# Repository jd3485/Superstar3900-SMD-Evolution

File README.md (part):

> **CONTINUITÀ CHATGPT WORK — CONFIGURAZIONE PERMANENTE (11/11/2026).** Nuove sessioni: leggere anzitutto [AGENTS.md](AGENTS.md) (mandato tecnico permanente e ciclo multi-revisione senza ripetere «continua») e [WORK_STATO_CORRENTE.md](00_Gestione_Progetto/WORK_STATO_CORRENTE.md) (checkpoint aggiornabile). Per configurare un Progetto ChatGPT Work usare [ISTRUZIONI_CHATGPT_PROJECT_WORK.md](00_Gestione_Progetto/ISTRUZIONI_CHATGPT_PROJECT_WORK.md). Nessun lavoro prosegue automaticamente dopo la fine della chat senza nuova sessione/attività, e NO FAB/TX resta attivo.

# SUPERSTAR 3900 SMD EVOLUTION — V7.21 PRE-LAYOUT PCB QUALITY GATES (NO FAB / NO TX)

**11 novembre 2026 · V7.21 integrata su `main` tramite [PR #21](https://github.com/jd3485/Superstar3900-SMD-Evolution/pull/21), squash merge `9805f110d0acf59e69f7f54e87e299248b99d96b`.** Decisione di progetto: prima verificare pacchetti reali, pad, alimentazioni e termica, poi creare un'unica PCB. Non promettere «zero errori» sulla base di un DRC non significativo.

**Audit sulla vera netlist KiCad9 a 7 fogli:** **132 componenti**, **84 footprint assegnati**, **48 mancanti** (46 MCU/CODEC, 2 connettori J100/J101 AUX). Fra gli 84 assegnati **F200** fusibile e **Y1** TCXO hanno nomi espliciti `NON_VALIDATO`/`UNVALIDATED`; tutti gli altri footprint non sono ancora vendor-certified. Il nuovo audit ha verificato **sei candidati primari sulle vere librerie KiCad9**: STM32G474RET6 LQFP64 10×10/64 pad, TLV320AIC3204 VQFN32 RHB 5×5/33 pad incluso **EP33**, quattro LDO TPS7A20 DBV SOT23-5/5 pad. CANDIDATI soltanto: nessuno assegnato agli schemi prima del confronto pin/land pattern.

**Rischio TERMICO:** 6 TPS7A2033PDBVR da 300mA max ciascuno, due nella AUX 5V e quattro nella MCU 5V tuttora separata; 5→3,3V a 300mA =0,51W su un LDO, con `RθJA JEDEC=187,1°C/W` DBV e 40°C ambient =`TJ≈135,4°C` nell'esempio, superiore a 125°C operativo. Non prova il consumo effettivo: impone budget corrente e verifica termica PCB. **Buck** TPS54202 2A, R101=100k/R102=13k3 -> nominale `5,077V`, scenario limiti VREF +R `4,863–5,298V`; eFuse TPS26600 limite configurabile e F200 1,5A candidato. Serve qualificare tutti i rail, fuses, input e RTN.

**CI KiCad9** [run 42986310630](https://github.com/jd3485/Superstar3900-SMD-Evolution/actions/runs/42986310630) **success**: **24 test nuovi +284 regressioni=308 Python PASS, 0 FAIL/0 SKIP**. Nessun modificatore di schema o PCB, root ERC **36 errori/340 warning**, 15 RX/MCU/AUX OPEN/HOLD. Artefatti CSV delle 48 impronte mancanti e 6 package candidati, schematics/netlist e JSON in `03_Verifiche/V7.21/`. Rapporto `03_Verifiche/V7.21/RAPPORTO_TECNICO_CAD_V7.21.md`, gate di rilascio `01_Specifiche/V7.21/PIANO_QUALITA_PCB_UNICA_GATES_V7_21.md`, workflow `.github/workflows/v721_full_board_foundations.yml`.

**PCB completa stimata ~10% invariata**, nessuna tavola/meccanica inventata e nessun sbroglio globale simulato. **Next V7.22:** creare versione CAD per i sei IC con pin-pad/EP33 verificati; sistemare 42 missing remaining, poi budget termico/ritorni; solo dopo real PCB unica. **NO FAB / NO GERBER / NO PCBWAY / NO TX**, SG48 e tutti i 15 contratti HOLD.

---

## STORICO README V7.20 E PRECEDENTI

# SUPERSTAR 3900 SMD EVOLUTION — V7.20 PLL NGSPICE / TI 270 CANALI / POWER ERC LEDGER (NO FAB / NO TX)

**11 novembre 2026 · V7.20 MERGED su `main` tramite [PR #20](https://github.com/jd3485/Superstar3900-SMD-Evolution/pull/20), squash commit `271cf7c84c0ceeb1e490ac44ff065147c76fbb4e`.** Ultimo avanzamento è una **verifica analogica del modello** e un audit sulle sei sorgenti POWER della schematica completa, non una PCB unica. **Gli schemi V7.19 e precedenti e il coupon RX rimangono invariati**.

**Evidenza reale:** [CI 42971210346](https://github.com/jd3485/Superstar3900-SMD-Evolution/actions/runs/42971210346) **success**: `ngspice` originale del filtro PLL, **501 punti AC 10Hz–1MHz**, confronto con modello nodale indipendente, errore relativo massimo **8,31×10⁻⁷**, riproduzione del nominale V0.6 4.015,5Hz/59,76° **solo alle ipotesi del modello**, **non TI PLLatinum Sim**. Analizzati tutti **270** canali Integer-N (N3631..3900, fPFD1,28MHz), **2430** casi Kvco/Icp ipotetici; in più secondo sweep su **KVCO tipico ufficiale TI** (SNAS740B Tab.135 Eq.4): 2 canali VCO3 /268 VCO4, CPG4 o8 => nominali 2,5mA senza readback firmware. Nel modello lineare con KVCO tipico: **3,814–4,678kHz crossover**, margine **58,63°–62,87°**, NON limiti garantiti, phase noise/spurie/lock time non simulati.

**Audit KiCad9 nativo sulle 6 alimentazioni senza power-output:** U200:1 `EFUSE_VIN`, U200:8 `EFUSE_RTN`, U2:1 `5V_RF_PREREGULATED`, U2:2 `GND_MAIN`, U6203:1 `5V_DIGITAL_FILTERED`, U6203:2 `GND`. Tutte **HOLD**, nessun PWR_FLAG o waiver, non cortocircuitare GND_MAIN/EFUSE_RTN. Root ERC invariato **36 errori/340 warning**, 15 interfacce OPEN/HOLD. **18 test V7.20 +266 storici=284 Python PASS**, 0 FAIL/skip.

Rapporto e JSON `03_Verifiche/V7.20/`, protocollo TI `01_Specifiche/V7.20/PROTOCOLLO_PLL_NGSPICE_TI_TYPICAL_POWER_HOLD_V7_20.md`, workflow `.github/workflows/v720_pll_spice_power_native.yml`. La PCB completa resta **~10% stimato**, senza sbroglio/routing globale. **Next V7.21:** qualificare 13,8V→eFuse→buck→LDO, ritorni di massa e impostazioni PLL reali, poi PLLatinum Sim / bench e 15 interfacce. **NO FAB / NO GERBER / NO PCBWAY / NO TX**.

---

## STORICO README V7.19 E PRECEDENTI

# SUPERSTAR 3900 SMD EVOLUTION — V7.19 PLL TI LOOP PIN-NET CORRECTION (NO FAB / NO TX)

**11 novembre 2026 · V7.19 integrata su `main` tramite [PR #19](https://github.com/jd3485/Superstar3900-SMD-Evolution/pull/19), squash merge `6d5ccb179cbe46760605edde6c44c2fc89a9ac5e`.** Avanzamento REALE dello schematico KiCad a 7 fogli: nuova copia versionata `04_KiCad/Assemblaggio_RX_Power_V7.19_PLL_PINNET_NOT_FOR_FAB/` con ramo AUX `04_KiCad/Gerarchico_Alimentazioni_V7.19_PLL_PINNET_NOT_FOR_FAB/`. Le versioni passate restano immutate. Nel SOLO foglio PLL sono aggiunte 6 etichette a pin R2/R3/C2/C3: topologia **TI LMX2572 datasheet Fig.179**: CPOUT=U1:12/R2:1/R3:1/C1:2, R2_C2=R2:2/C2:2, VTUNE=U1:35/R3:2/C3:2. Nessun filo, nuova rete di power, intermodulo, TX o PCB aggiunti.

**Prova native KiCad 9:** [CI 42967147073](https://github.com/jd3485/Superstar3900-SMD-Evolution/actions/runs/42967147073) **PASS**: V7.18 42 errori/340 avvisi → V7.19 **36 errori/340 avvisi**, 99→**100 reti** (sola nuova `PLL_R2_C2`), -2 pin_not_connected, -3 wire_dangling, -1 input_not_driven; **nessun ref/pin cambiato fuori da tre reti del filtro**. **13 test nuovi +253 storici =266 Python PASS**, 0 falliti/skip. Nessuna nuova simulazione analogica o prova hardware.

**ATTENZIONE:** i valori R2 620Ω/R3 22Ω/C1 220p/C2 120n/C3 2.2n e margine fase/rumore VCO sono ancora HOLD: il contratto verifica esclusivamente le reti CAD, non valida PLLatinum Sim o layout RF. 36 ERC root aperti (26 label, 6 alimentazioni, 4 input), 340 warning, 15 interfacce OPEN/HOLD, RX_IF_STAGE ancora mancante, SG48 e TX HOLD, SMA 180° da qualificare. **PCB completa ~10%, invariato:** nessun PCB globale esistente.

Rapporto `03_Verifiche/V7.19/RAPPORTO_TECNICO_CAD_V7.19.md`, JSON e artifact `v719-real-kicad-ti-loop-pin-forensics-NO-FAB-NO-TX`; fonte TI `01_Specifiche/V7.19/PIANO_PINNET_LOOP_PLL_TI_V7_19.md`. Next V7.20: simulazione PLL per stabilità e qualifiche alimentazione/ritorni, poi interfacce e vero layout PCB. **NO FAB / NO GERBER / NO PCBWAY / NO TX**.

---

## STORICO README V7.18 E PRECEDENTI

# SUPERSTAR 3900 SMD EVOLUTION — V7.18 eFuse ERC / PLL LOOP NATIVE AUDIT (NO FAB / NO TX)

**11 novembre 2026 · V7.18 integrata su `main` tramite [PR #18](https://github.com/jd3485/Superstar3900-SMD-Evolution/pull/18), merge `29965cdcdfe2edd1e241295315bfe18fabc864a5`.** Ora l'integrazione schematico intera radio a 7 fogli include una **copia KiCad V7.18 con modifica reale, strettamente limitata, del modello elettrico TPS26600 OUT16**; nessun routing o PCB unica è stato creato.

**Dato tecnico validato da TI:** nel TPS26600PWPT HTSSOP, i pin OUT **15 e 16 sono due terminali della stessa uscita fisica** (datasheet SLVSDG2G p.5). L'ECO nel simbolo embedded su copia `04_KiCad/Gerarchico_Alimentazioni_V7.18_PINMODEL_NOT_FOR_FAB/` rende il solo pin16 `passive` per l'ERC di KiCad, mentre pin15 resta `power_out`, entrambi restano sullo stesso `BUCK_VIN_PROTECTED`. La versione storica V1.5 è byte-intatta e non si separano i pin.

**KiCad9 nativo** [run 42964160297](https://github.com/jd3485/Superstar3900-SMD-Evolution/actions/runs/42964160297) **success**: root ERC prima **43 errori/340 warning** → versione V7.18 **42 errori/340 warning**; l'unico errore eliminato è `pin_to_pin` fra le due uscite della stessa U200, **99 net e tutti i ref/pin elettricamente identici**. RX e firmware/DSP/PLL baseline non modificati. **12 nuovi test +241 precedenti =253 Python PASS, 0 FAIL/0 SKIP**.

**Loop-filter R2/R3:** quattro test KiCad9 su cloni temporanei del progetto completo; nessun esperimento ha eliminato errori: baseline 42/340, R2 filo esterno 42/341, R3 rotazione 42/340, combinazione 42/341, tutte le netlist di ref/pin invariate. **Nessuna di queste prove viene messa in produzione o applicata alla schematica.** Restano 26 label e 16 altri errori elettrici/fili, 15 interfacce OPEN/HOLD, stadio RX_IF mancante e SMA J9102/J9104 non qualificati.

Nuovo master: `04_KiCad/Assemblaggio_RX_Power_V7.18_POWER_PINMODEL_NOT_FOR_FAB/`. Rapporto `03_Verifiche/V7.18/RAPPORTO_TECNICO_CAD_V7.18.md`, JSON `RISULTATI_VERIFICHE_V7_18.json`, specifica `01_Specifiche/V7.18/ECO_EFUSE_DUAL_OUT_PINMODEL_V7_18.md`, workflow `.github/workflows/v718_efuse_pll_native.yml`. Percentuale PCB completa **~10% invariata**, perché non esiste ancora una PCB unica sbrogliata. Next V7.19: ricostruire filtro PLL e i 16 errori hard per completare schema e interfacce prima del layout. **NO FAB / NO GERBER / NO TX**.

---

## STORICO README V7.17 E PRECEDENTI

# SUPERSTAR 3900 SMD EVOLUTION — V7.17 FULL-RADIO KICAD INTEGRATION GATE (NO FAB / NO TX)

**11 novembre 2026 · V7.17 integrata su `main` tramite [PR #17](https://github.com/jd3485/Superstar3900-SMD-Evolution/pull/17), merge `ff26db4e55eb2ab7368cb222de58a8b969cf08d6`.** Il lavoro passa dal solo RX al **master schematico gerarchico per la radio completa**, ma resta senza cablaggi intermodulo e senza PCB unica. La stima di avanzamento layout PCB completa rimane **~10%**: questo è progresso di diagnosi e contratto, non routing/produzione.

**Prova vera KiCad9:** [run 42923409956](https://github.com/jd3485/Superstar3900-SMD-Evolution/actions/runs/42923409956) PASS. Nuovo master `04_KiCad/Assemblaggio_RX_Power_V7.17_INTEGRATION_HOLD_NOT_FOR_FAB/`: 7 pagine, **99 reti e ogni ref/pin identici alla V7.14**, nessun nuovo wire/port/rail o TX, native root ERC invariato **43 errori/340 warning**, RX ERC **0/0**. **18 test nuovi +223 regressioni =241 PASS, 0 FAIL/0 SKIP**; nessun test Icarus/Yosys/RF nuovo.

**Contratto 15 interfacce TUTTE OPEN/HOLD:** sola rettifica candidata del nome FM lato MCU `FM_DISCR_RAW` → `FM_DISCRIM_RAW` già esistente nel vero schema. Nessuna connessione reale effettuata. Mancano tuttora `RX_IF_STAGE` (catena RX→IF da progettare) e `RF_TX_UNROUTED` (TX volutamente non presente). Rail 5V/3V3 e GND da qualificare, 17 errori ERC a livello elettrico/fili e 26 label. Report e JSON `03_Verifiche/V7.17/`, workflow `.github/workflows/v717_full_board_erc.yml`.

**Prossimo:** V7.18 affrontare ERC fisici POWER/PLL e collegamenti SPI solo dopo verifica datasheet/pinout, poi 15 interfacce, schema completo e primo layout PCB reale della radio. **NO FAB / NO GERBER / NO PCBWAY / NO TX.**

---

## STORICO README V7.16 E PRECEDENTI

# SUPERSTAR 3900 SMD EVOLUTION — V7.16 DIAGNOSI ORIENTAMENTO SMA (NO FAB / NO TX)

**10 novembre 2026 · V7.16 integrata su `main` con [PR #16](https://github.com/jd3485/Superstar3900-SMD-Evolution/pull/16), merge `b8ad95695aed960621f4fd2160fa4b2ae921d6eb`. Verificare sempre HEAD di `main`.** È un avanzamento **diagnostico CAD nativo** e NON un PCB aggiornato/producibile.

**Progresso reale:** l'ultimo DRC KiCad9 su quattro cloni temporanei con zone riempite ha verificato la causalità del mismatch SMA J9102/J9104. Con posizione e orientamento originari 180°: **2 `lib_footprint_mismatch` +0 unconnected**; ruotando solo le etichette o i custom pad: ancora **2+0**; forzando entrambi gli SMA destro a orientamento 0°: **0+0**, ma la *direzione fisica dei connettori sul lato destro diventa SBAGLIATA*. Il courtyard corretto sporge oltre il bordo x130 sino a x137,2 mm; quello a 0° rientra nell'area fino a x126,1. **Non applicare il workaround**: la correzione deve preservare il montaggio a 180°. Il PCB sorgente storico e le sue net, piste/via/simboli sono invariati.

**Evidenza CI** [run 42920876308](https://github.com/jd3485/Superstar3900-SMD-Evolution/actions/runs/42920876308): **10 nuovi test +213 regressioni =223 Python PASS, 0 FAIL/0 SKIP**; quattro DRC nativi misurati con KiCad9. Icarus/Yosys/hardware RF non rieseguiti. Sorgenti nuovi `03_Verifiche/V7.16/`, rapporto `03_Verifiche/V7.16/RAPPORTO_TECNICO_CAD_V7.16.md`, JSON `03_Verifiche/V7.16/RISULTATI_VERIFICHE_V7_16.json`, specifica `01_Specifiche/V7.16/PROTOCOLLO_SMA_ORIENTAMENTO_KICAD_V7_16.md`. Prima baselines: RX ERC 0/0, root 43 errori +340 warning, 15 interfacce OPEN/HOLD e SG48 HOLD.

**Vendor:** il produttore TE Connectivity/Linx pubblica disegno Rev D e CAD ufficiali DXF/STEP per `CONSMA002-SMD`; questi archivi non sono stati importati/validati e nessuna impronta è qualificata per produzione. **Prossima V7.17:** acquisire e confrontare DXF/STEP per J9102/J9104, risolvere mismatch KiCad mantenendo 180°, verificare ingombro, ritorni GND_RF e zone-fill su un nuovo PCB versionato. NO FAB / NO PCBWAY / NO GERBER / NO TX.

---

## ARCHIVIO V7.15 E PRECEDENTI

# SUPERSTAR 3900 SMD EVOLUTION — V7.15 REFILL GND DIAGNOSTICO, NO FAB / NO TX

**10 novembre 2026 · V7.15 integrata in `main` con [PR #15](https://github.com/jd3485/Superstar3900-SMD-Evolution/pull/15), merge `ca81deb3fe83e210778590cc9e2db1a18e16b243`. Verificare sempre HEAD `main`.** Storico e tag `v7.0` conservati. Questo è un avanzamento DIAGNOSTICO REALE, **non una PCB di produzione né una radio finita**.

**Risultato nativo KiCad sorprendente ma documentato:** 70 via GND_RF dangling e63 unconnected DRC della V7.14 derivavano dal test su zone **non salvate come copper fill**. La CI V7.15 ha riempito le quattro zone con il vero `pcbnew.ZONE_FILLER` in una copia TEMPORANEA integrale del progetto (nessuna variazione del PCB sorgente, SHA256 invariato), poi `kicad-cli pcb drc` ha misurato **72→2 violazioni** e **63→0 unconnected**; **J9102/J9104 lib_footprint_mismatch rimangono 2**. Si tratta di prova sul clone, non di correzioni CAD persistite o qualifica fisica. `--refill-zones` non era supportato dal CLI della CI ed è registrato NON ESEGUITO, sostituito da una reale prova con pcbnew.

**SMA vendor:** confronto con TE/Linx CONSMA002-SMD, disegno Rev D p.2/3: centro Ø2,05 mm e dimensione nominale trasversale 7,76 mm parzialmente compatibili. Tutti i pad KiCad locali risultano di forma identica alla libreria, inclusi J9102/J9104 ruotati 180°; la causa vera dei due warning non è stata ancora qualificata. CAD manufacturer DXF/STEP, assembly, pastemask, GND return/RF stackup NON approvati.

**CI:** [push run 42918178033](https://github.com/jd3485/Superstar3900-SMD-Evolution/actions/runs/42918178033) e [PR run 42918302874](https://github.com/jd3485/Superstar3900-SMD-Evolution/actions/runs/42918302874), **12 test nuovi +201 regressioni =213 Python PASS**, ERC RX **0/0**, root ERC **43 errori/340 warning** (BLOCCANTE). Icarus/Yosys non rieseguiti; no hardware RF/EMC. Rapporto `03_Verifiche/V7.15/RAPPORTO_TECNICO_CAD_V7.15.md`, JSON `03_Verifiche/V7.15/RISULTATI_VERIFICHE_V7_15.json`, spec `01_Specifiche/V7.15/SMA_ZONE_READONLY_DIAGNOSTIC_V7_15.md`. Il progetto RX originale rimane byte-identico; **zero Gerber, NO FAB / NO TX**.

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
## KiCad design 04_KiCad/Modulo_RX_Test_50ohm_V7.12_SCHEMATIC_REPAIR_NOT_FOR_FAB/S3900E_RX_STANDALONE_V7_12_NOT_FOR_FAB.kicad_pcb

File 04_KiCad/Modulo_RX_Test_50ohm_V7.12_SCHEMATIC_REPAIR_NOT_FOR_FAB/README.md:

# KiCad V7.12 — RX coupon standalone repaired and schematic/PCB refs consistent

The two native files are meant for **KiCad 9**:
- `S3900E_RX_STANDALONE_V7_12_NOT_FOR_FAB.kicad_sch`: repaired copy of legacy RX V5.2, all 15 refs +9000 and project instances aligned.
- `S3900E_RX_STANDALONE_V7_12_NOT_FOR_FAB.kicad_pcb`: copy of RX V7.11 with **same 15 refs**, unchanged pads, nets, via positions and drill diameters. Six GND via Ø0.30 mm fixes from V7.11 retained.

Actual standalone parser root cause: legacy graphical `(text)` contained raw LF characters inside a quoted S-expression string and lacked a UUID. KiCad `sch erc` returned **exit3 Failed to load schematic**. V7.12 text now uses escaped literal `\\n`, supplies its UUID and includes sheet root metadata; **native standalone ERC now loads (exit0)** and returns **0 errors +76 warnings**: 46 off-grid endpoints, 15 footprint links, 15 symbol library issues. This is NOT clean ERC.

Actual KiCad native PCB DRC still returns **85 violations** (70 dangling vias, 15 footprint warnings) plus **63 unconnected**, not DRC clean. The local `fp-lib-table` lists existing library paths and does not certify any SMD land pattern or SMA/LNA assembly.

All original KiCad files are preserved. No crossmodule nets or RF TX hardware added. **NO FAB / NO TX.**

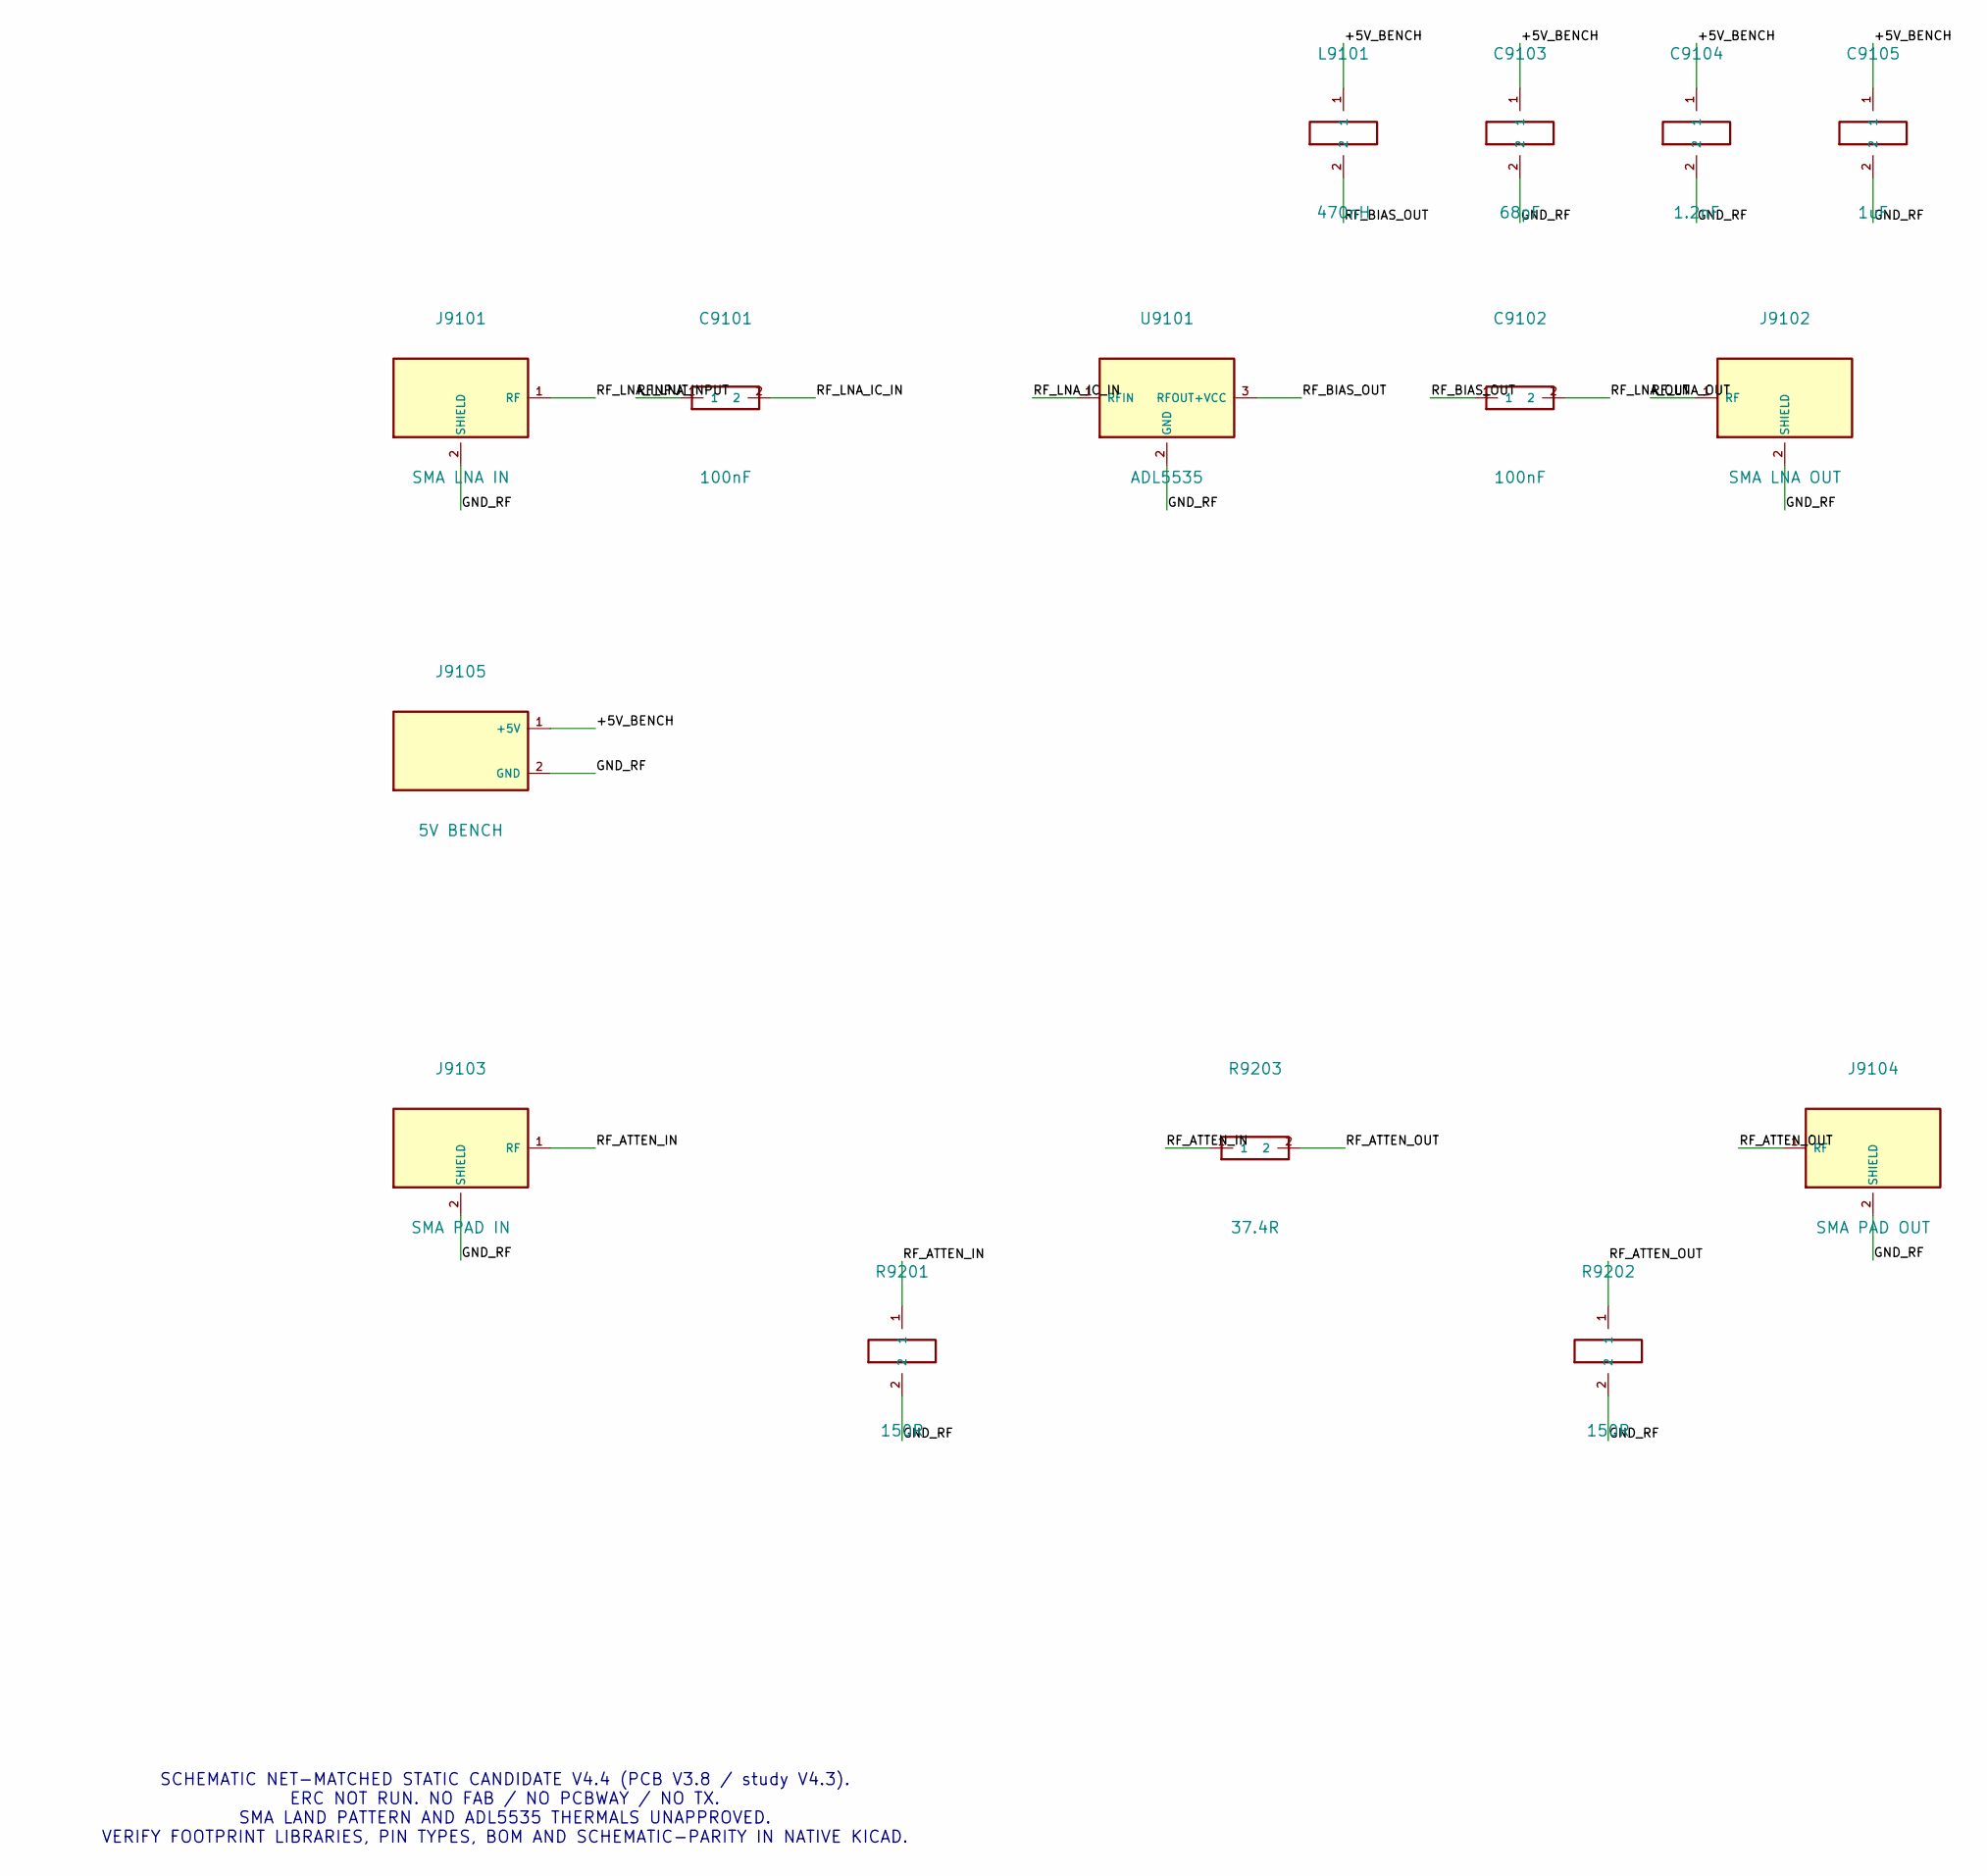
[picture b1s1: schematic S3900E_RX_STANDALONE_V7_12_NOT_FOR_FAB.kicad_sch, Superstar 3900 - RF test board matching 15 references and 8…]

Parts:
C9101, C9102: 100nF; C_0402
C9103: 68pF; C_0603
C9104: 1.2nF; C_0603
C9105: 1uF; C_1206
J9101: SMA LNA IN; CONSMA002_SMD_SHAPED_REVIEW
J9102: SMA LNA OUT; CONSMA002_SMD_SHAPED_REVIEW
J9103: SMA PAD IN; CONSMA002_SMD_SHAPED_REVIEW
J9104: SMA PAD OUT; CONSMA002_SMD_SHAPED_REVIEW
J9105: 5V BENCH; 2_wire_solder_pads
L9101: 470nH; L_0603
R9201, R9202: 150R; R_0402_SHUNT_PERPENDICULAR
R9203: 37.4R; R_0402
U9101: ADL5535; ADL5535_SOT89_PASTE_REVIEW

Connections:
+5V_BENCH: C9103.1, C9104.1, C9105.1, J9105.1 (+5V), L9101.1
GND_RF: C9103.2, C9104.2, C9105.2, J9101.2 (SHIELD), J9102.2 (SHIELD), J9103.2 (SHIELD), J9104.2 (SHIELD), J9105.2 (GND), R9201.2, R9202.2, U9101.2 (GND)
RF_ATTEN_IN: J9103.1 (RF), R9201.1, R9203.1
RF_ATTEN_OUT: J9104.1 (RF), R9202.1, R9203.2
RF_BIAS_OUT: C9102.1, L9101.2, U9101.3 (RFOUT+VCC)
RF_LNA_IC_IN: C9101.2, U9101.1 (RFIN)
RF_LNA_INPUT: C9101.1, J9101.1 (RF)
RF_LNA_OUT: C9102.2, J9102.1 (RF)

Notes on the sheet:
SCHEMATIC NET-MATCHED STATIC CANDIDATE V4.4 (PCB V3.8 / study V4.3). ERC NOT RUN. NO FAB / NO PCBWAY / NO TX. SMA LAND PATTERN AND ADL5535 THERMALS UNAPPROVED. VERIFY FOOTPRINT LIBRARIES, PIN TYPES, BOM AND SCHEMATIC-PARITY IN NATIVE KICAD.

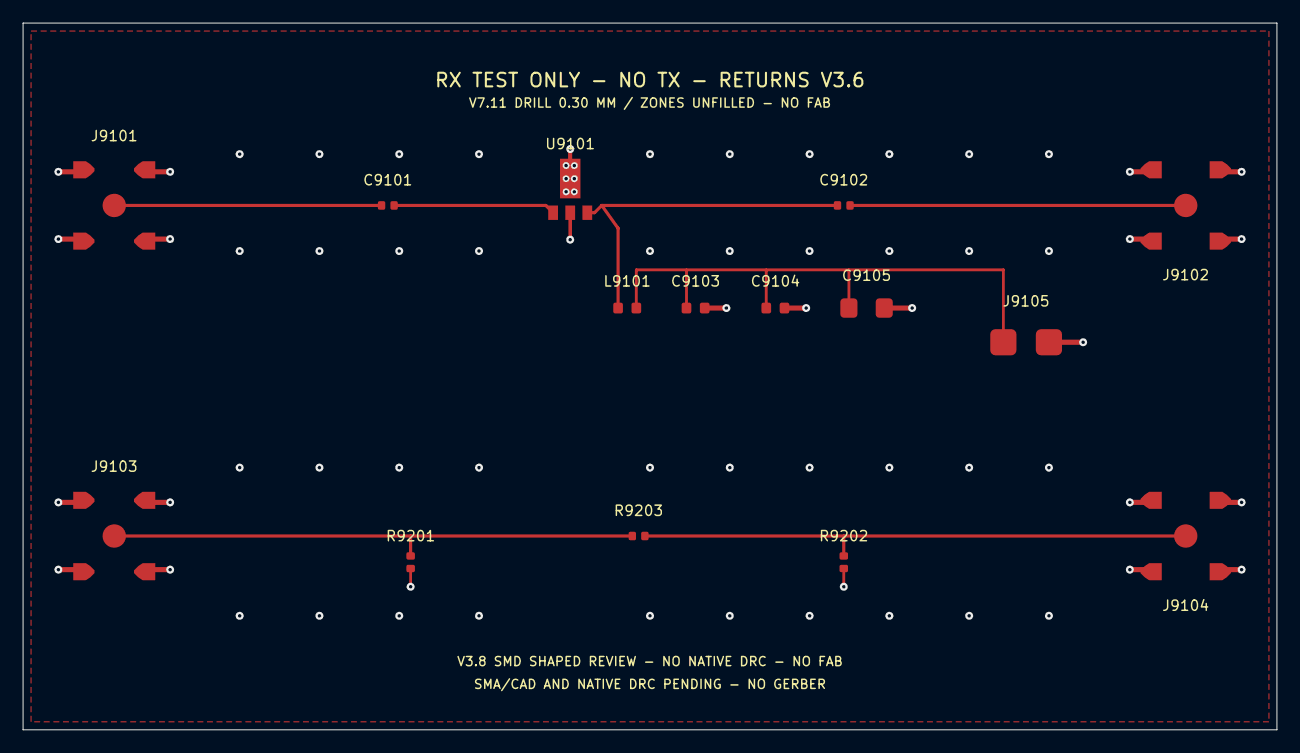
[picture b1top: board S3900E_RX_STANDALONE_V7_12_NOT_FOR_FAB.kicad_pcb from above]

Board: 4 copper layers, 110.0 x 62.0 mm, 15 parts (0 on the bottom side), 8 nets.

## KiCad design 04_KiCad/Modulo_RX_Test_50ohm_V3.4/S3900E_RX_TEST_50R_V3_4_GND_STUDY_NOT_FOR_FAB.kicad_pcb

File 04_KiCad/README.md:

# Sezione KiCad — non ancora generata

Qui saranno inseriti schemi gerarchici, PCB, simboli/footprint personalizzati, note meccaniche e report ERC/DRC. I principali fogli pianificati sono:
- ingresso RF, T/R, preselettori e protezione;
- sintonia/PLL/VCO;
- ricevitori FI, filtri e demodulazione;
- catena TX, amplificatore e LPF;
- accoppiatore direzionale e ATU LC con bypass;
- alimentazioni e protezioni;
- microcontrollore, display, comandi fisici, indicatori e audio.

L'architettura modulare potrà richiedere più PCB, da decidere dopo ingombri e budget interferenze.
**Non considerare il progetto producibile prima di una distinta componenti validata, ERC/DRC e revisioni specifiche RF.**

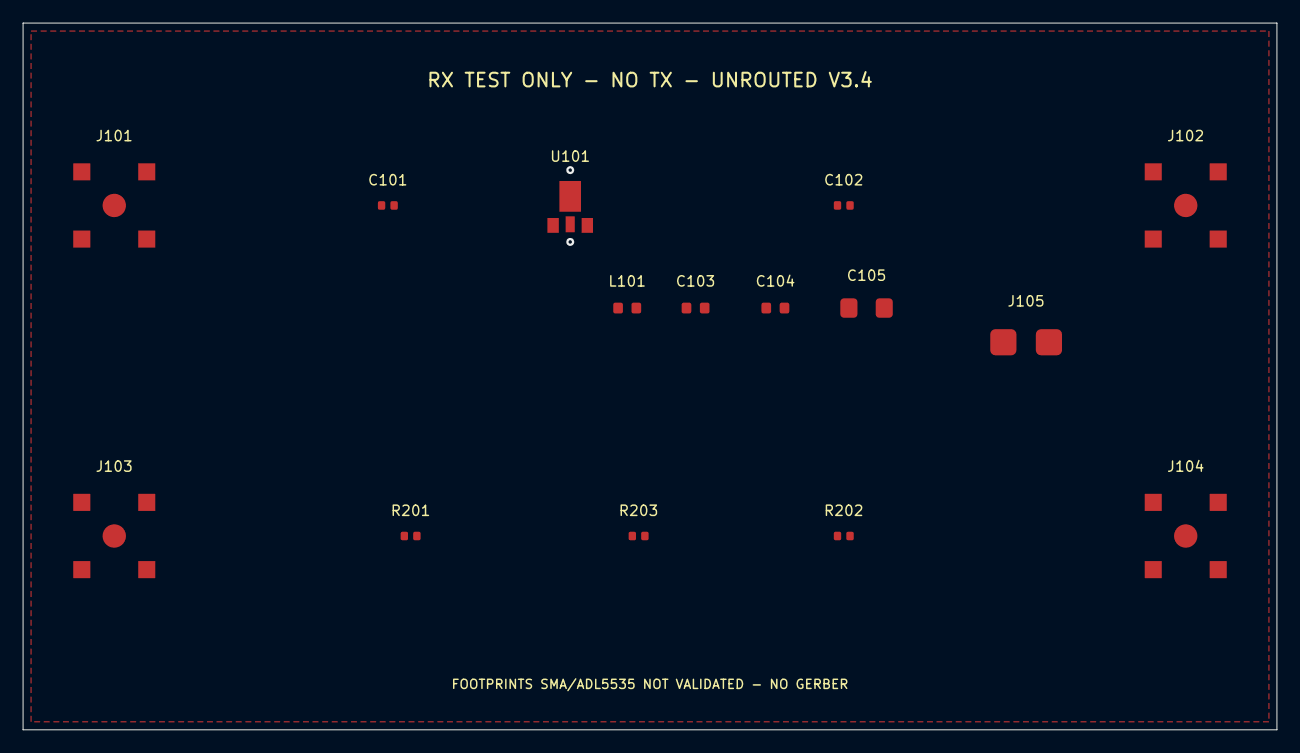
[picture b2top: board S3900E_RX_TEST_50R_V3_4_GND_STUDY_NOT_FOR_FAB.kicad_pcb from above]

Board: 4 copper layers, 110.0 x 62.0 mm, 15 parts (0 on the bottom side), 8 nets, no tracks yet.

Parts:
C101, C102: 100nF; C_0402
C103: 68pF; C_0603
C104: 1.2nF; C_0603
C105: 1uF; C_1206
J101: SMA LNA IN; SMA_5pad_Placeholder
J102: SMA LNA OUT; SMA_5pad_Placeholder
J103: SMA PAD IN; SMA_5pad_Placeholder
J104: SMA PAD OUT; SMA_5pad_Placeholder
J105: 5V BENCH; 2_wire_solder_pads
L101: 470nH; L_0603
R201, R202: 150R; R_0402
R203: 37.4R; R_0402
U101: ADL5535; SOT89_3

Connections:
+5V_BENCH: C103.1, C104.1, C105.1, J105.1, L101.2
GND_RF: C103.2, C104.2, C105.2, J101.2, J102.2, J103.2, J104.2, J105.2, R201.2, R202.2, U101.2
RF_ATTEN_IN: J103.1, R201.1, R203.1
RF_ATTEN_OUT: J104.1, R202.1, R203.2
RF_BIAS_OUT: C102.1, L101.1, U101.3
RF_LNA_IC_IN: C101.2, U101.1
RF_LNA_INPUT: C101.1, J101.1
RF_LNA_OUT: C102.2, J102.1
